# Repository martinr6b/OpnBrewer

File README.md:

# 🍵OpnBrewer
[)](https://discord.gg/c2CaMQDF9t)

<br></br>
## Work in progress
## ABOUT
This project was only started because i was bored, and it's a good way for me to gain some experience. This is so far only being made 100% compatible with the EDG355.B1 model of Nescafe dolce gusto machines
<br></br>
## FEATURES
- rgb led indicator
- home assistant integration using [ESPHOME](https://esphome.io 'esphome main page')
- auto power off
- fully customizable
- thermosat integration for adjustable target temp
- all safety features implemented (when final version)
<br></br>
## Compatibility
- So far only verified working with the **Nescafe dolce gusto EDG355.B1**
- I intend do make it compatible with many more models in the future
<br></br>
## HOW-TO
- TODO (lol)
<br></br>
## PROGRESS

This is the way the Coffee machine is currently exposed to Home Assistant
<br></br>
## TODO 
- Fix delayed temperature readings
- Order Power Supply PCB
- Finish Top PCB

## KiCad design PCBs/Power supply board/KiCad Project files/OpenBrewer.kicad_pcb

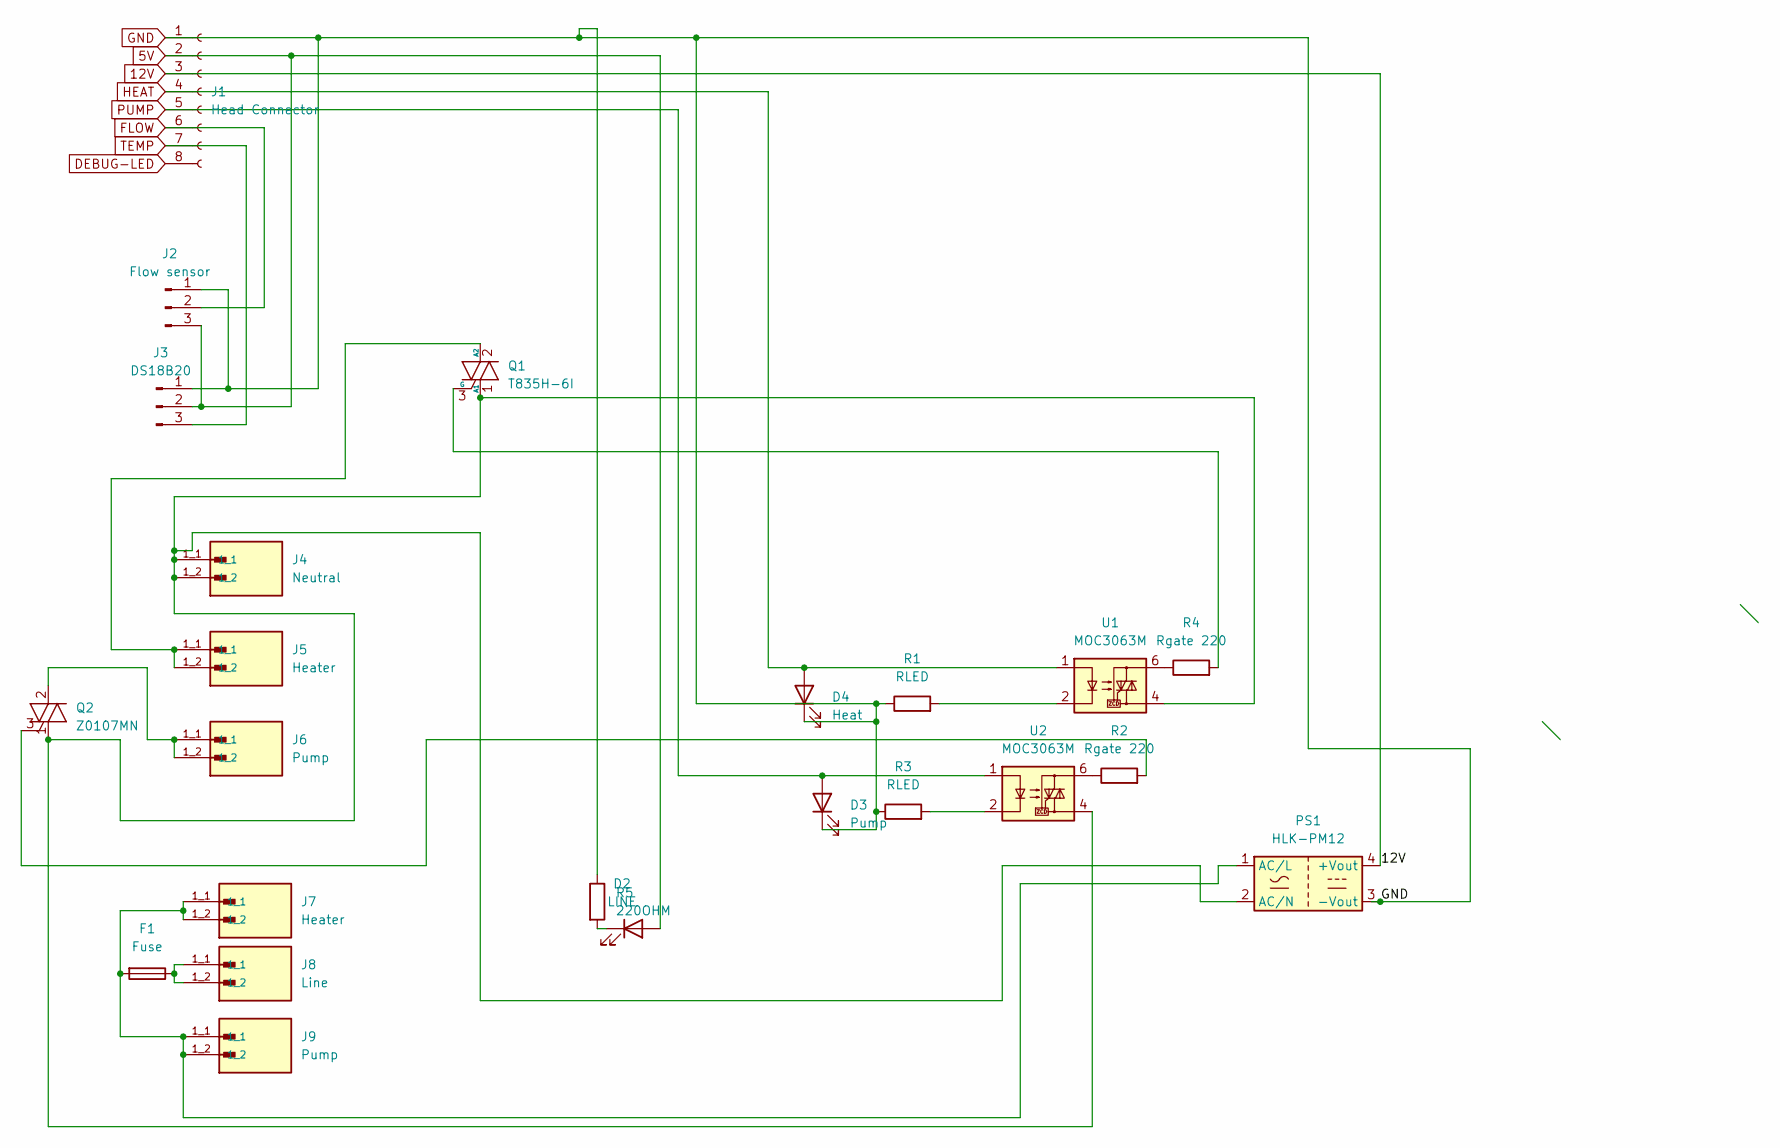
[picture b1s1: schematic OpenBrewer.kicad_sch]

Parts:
D2: LINE; LED_D3.0mm
D3: Pump; LED_D3.0mm
D4: Heat; LED_D3.0mm
F1: Fuse; Fuseholder_Cylinder-5x20mm_Schurter_0031_8201_Horizontal_Op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
J1: Head Connector; JST_PH_B8B-PH-K_1x08_P2.00mm_Vertical
J2: Flow sensor; JST_PH_B3B-PH-K_1x03_P2.00mm_Vertical
J3: DS18B20; JST_PH_B3B-PH-K_1x03_P2.00mm_Vertical
J4: Neutral; KEYSTONE_1212-ST; PARTREV C
J5, J7: Heater; KEYSTONE_1212-ST; PARTREV C
J6, J9: Pump; KEYSTONE_1212-ST; PARTREV C
J8: Line; KEYSTONE_1212-ST; PARTREV C
PS1: HLK-PM12; Converter_ACDC_Hi-Link_HLK-PMxx
Q1: T835H-6I; TO-220-3_Vertical
Q2: Z0107MN; SOT-223
R1, R3: RLED; R_1206_3216Metric_Pad1.30x1.75mm_HandSolder
R2, R4: Rgate 220; R_0201_0603Metric_Pad0.64x0.40mm_HandSolder
R5: 220OHM; R_0603_1608Metric_Pad0.98x0.95mm_HandSolder
U1, U2: MOC3063M; DIP-6_W10.16mm_LongPads

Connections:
5V: D2.2 (A), J1.2, J2.3, J3.2
12V: J1.3, PS1.4 (+Vout)
DEBUG-LED: J1.8
FLOW: J1.6, J2.2
GND: D3.1 (K), D4.1 (K), J1.1, J2.1, J3.1, PS1.3 (-Vout), R1.1, R3.1, R5.1
HEAT: D4.2 (A), J1.4, U1.1
unnamed: D2.1 (K), R5.2
unnamed: F1.1, J8.1_1, J8.1_2
unnamed: F1.2, J7.1_1, J7.1_2, J9.1_1, J9.1_2, PS1.1 (AC/L)
unnamed: J4.1_1, J4.1_2, PS1.2 (AC/N), Q1.1 (A1), Q2.1 (A1), U1.4, U2.4
unnamed: J5.1_1, J5.1_2, Q1.2 (A2)
unnamed: Q1.3 (G), R4.2
unnamed: J6.1_1, J6.1_2, Q2.2 (A2), Q2.4 (A4)
unnamed: Q2.3 (G), R2.2
unnamed: R1.2, U1.2
unnamed: R2.1, U2.6
unnamed: R3.2, U2.2
unnamed: R4.1, U1.6
PUMP: D3.2 (A), J1.5, U2.1
TEMP: J1.7, J3.3

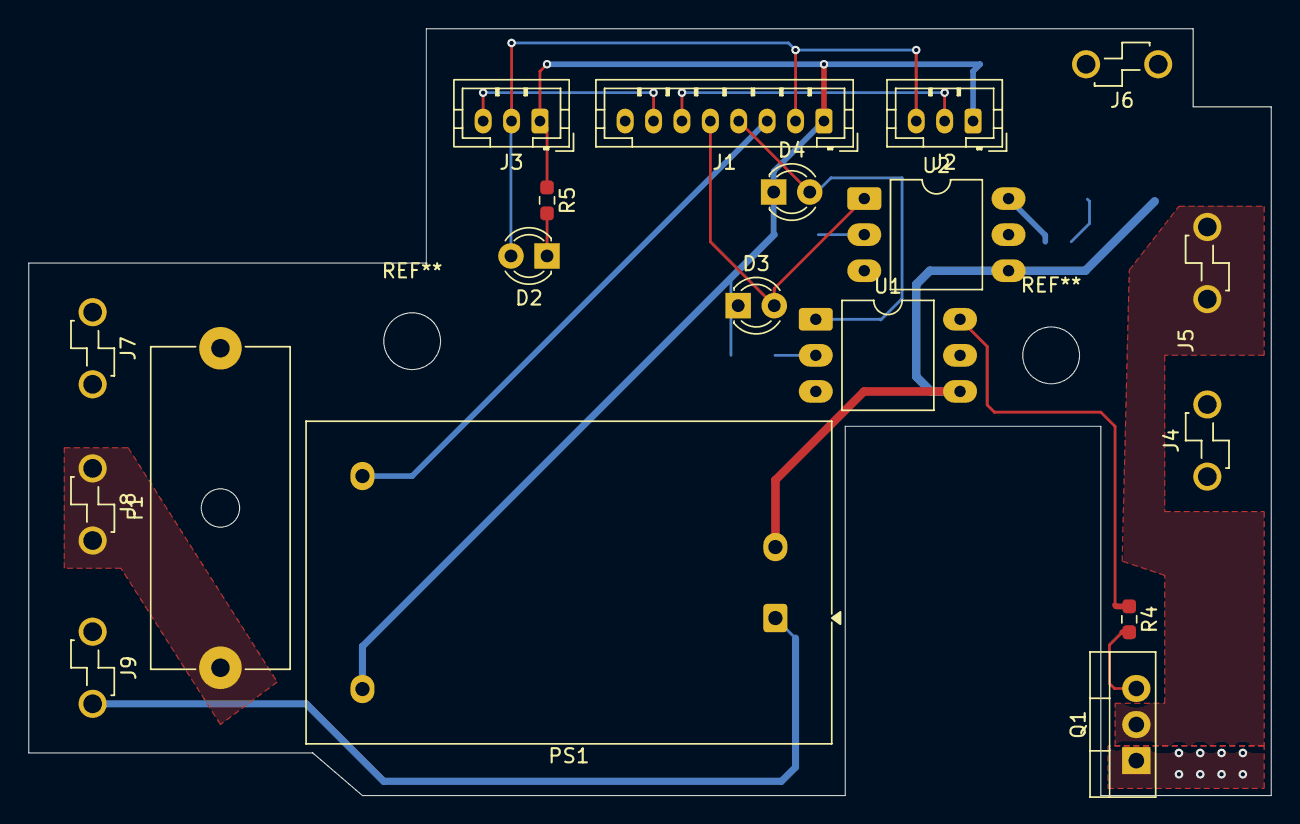
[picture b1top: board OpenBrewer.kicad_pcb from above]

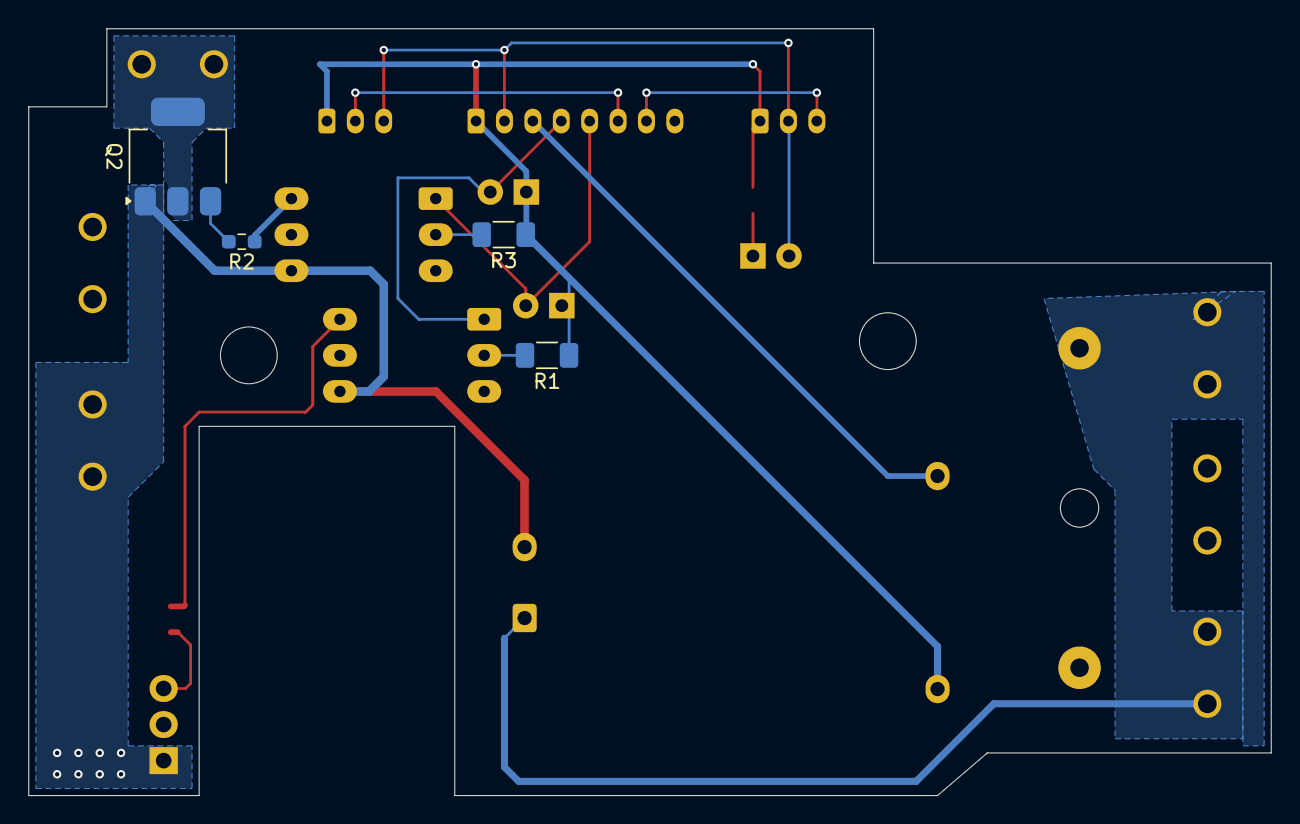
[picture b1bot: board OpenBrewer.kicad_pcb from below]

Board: 2 copper layers, 87.5 x 54.0 mm, 23 parts (4 on the bottom side), 19 nets.

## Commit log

2025-03-02 Update README.md
    added work in progress tiktok and discord
2025-05-24 Update README.md
    about,fetures
2025-05-24 Update README.md
    added ESPHOME link
2025-05-24 Update README.md
    added screenshot and progress
2025-06-21 Update README.md
    +1 feature
2025-06-21 Update README.md
    how to update
2025-06-21 remove private api key change wifi fallback PWD
2025-06-21 Create images
2025-06-21 Create gfdg
2025-06-21 add images to image dir
2025-06-21 add status light images
2025-06-21 Update README.md
    yes
2026-01-16 Clean up smart-coffee.yaml
    Removed unnecessary whitespace and comment.
2026-01-20 Refactor smart-coffee.yaml configuration
    Updated encryption key, modified RGB light colors, and adjusted climate control settings for hot and cold switches.
2026-01-20 Progress picture
2026-01-20 Add README.md to OLD directory for clarification
2026-01-20 Moved old pictures, changed readme exposes screenshot
2026-01-20 Fix IMAGE
2026-01-20 Readme work
2026-01-20 fix typo and add breaks
2026-01-20 more patchwork
2026-01-20 fix image size
2026-01-20 Added images
2026-01-20 Added board designs
2026-01-20 added gerbers
